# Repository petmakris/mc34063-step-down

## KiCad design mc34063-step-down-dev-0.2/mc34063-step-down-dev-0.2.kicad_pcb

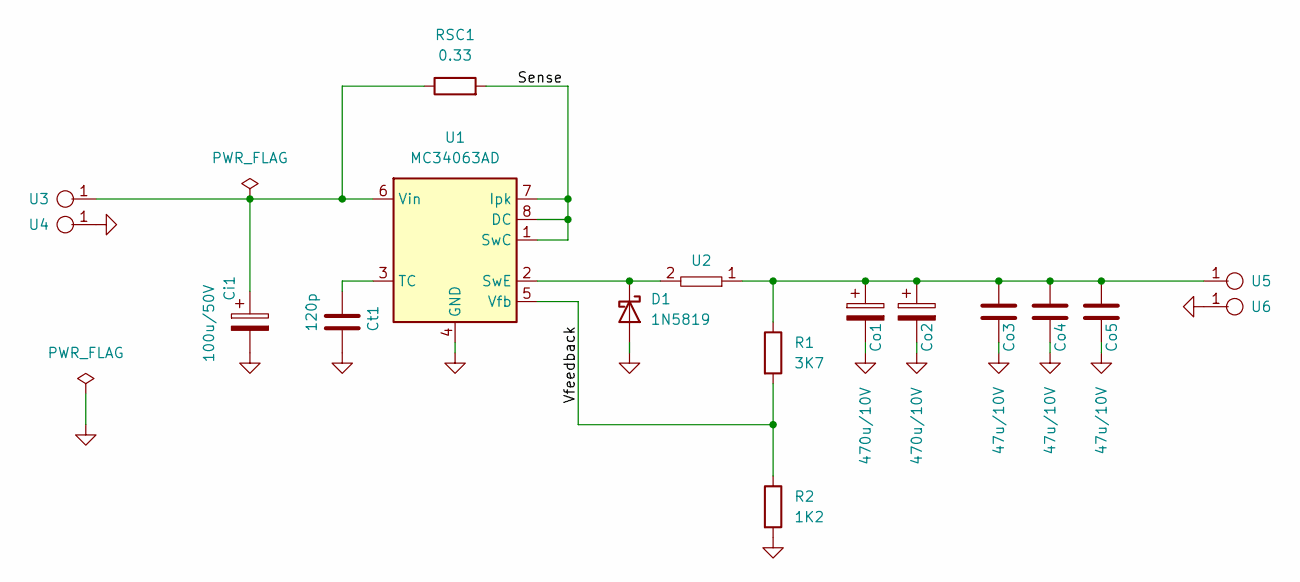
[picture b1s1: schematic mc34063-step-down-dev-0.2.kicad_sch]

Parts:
Ci1: 100u/50V; CP_Elec_6.3x7.7
Co1, Co2: 470u/10V; CP_Elec_6.3x7.7
Co3, Co4, Co5: 47u/10V; C_1206_3216Metric_Pad1.33x1.80mm_HandSolder
Ct1: 120p; C_0805_2012Metric_Pad1.18x1.45mm_HandSolder
D1: 1N5819; D_SOD-123
R1: 3K7; R_0805_2012Metric_Pad1.20x1.40mm_HandSolder
R2: 1K2; R_0805_2012Metric_Pad1.20x1.40mm_HandSolder
RSC1: 0.33; R_0805_2012Metric_Pad1.20x1.40mm_HandSolder
U1: MC34063AD; SOIC-8_3.9x4.9mm_P1.27mm
U2: mc34063-power-inductor-leaded
U3, U4, U5, U6: 1pin

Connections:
/Sense: RSC1.2, U1.1 (SwC), U1.7 (Ipk), U1.8 (DC)
/Vfeedback: R1.2, R2.1, U1.5 (Vfb)
GND: Ci1.2, Co1.2, Co2.2, Co3.2, Co4.2, Co5.2, Ct1.2, D1.2 (A), R2.2, U1.4 (GND), U4.1, U6.1
unnamed: Ci1.1, RSC1.1, U1.6 (Vin), U3.1
unnamed: Co1.1, Co2.1, Co3.1, Co4.1, Co5.1, R1.1, U2.1, U5.1
unnamed: Ct1.1, U1.3 (TC)
unnamed: D1.1 (K), U1.2 (SwE), U2.2

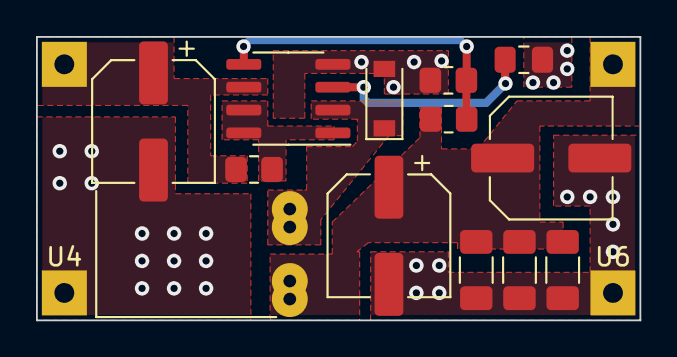
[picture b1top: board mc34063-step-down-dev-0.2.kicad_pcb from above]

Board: 2 copper layers, 33.5 x 15.7 mm, 17 parts (0 on the bottom side), 7 nets.

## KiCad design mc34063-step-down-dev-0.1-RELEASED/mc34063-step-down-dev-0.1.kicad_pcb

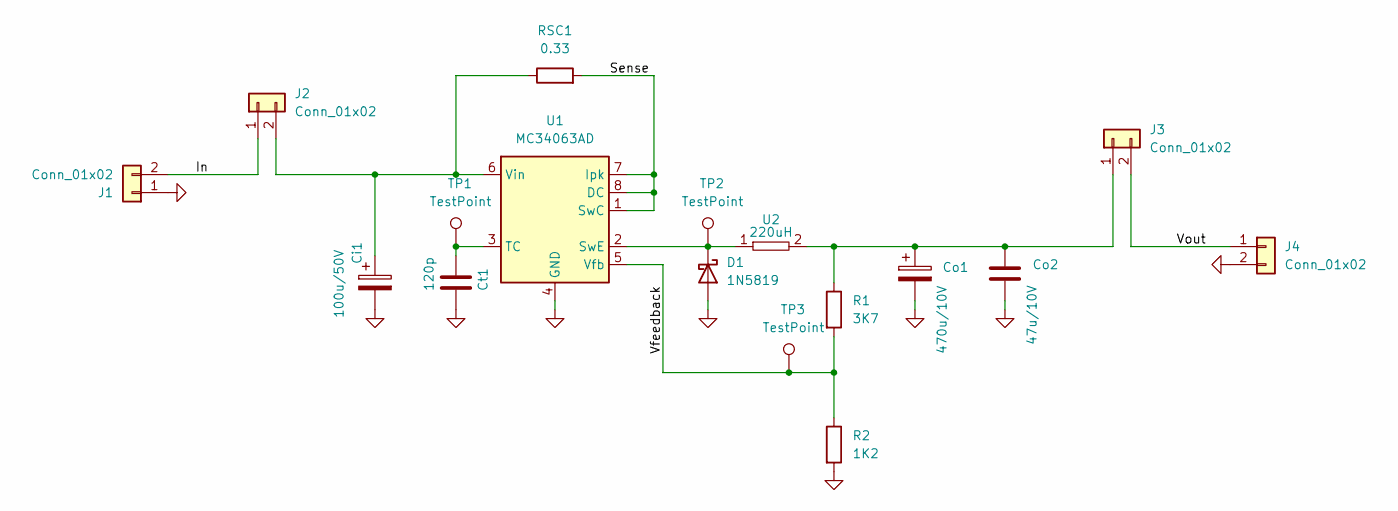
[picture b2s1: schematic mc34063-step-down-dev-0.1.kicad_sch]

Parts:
Ci1: 100u/50V; CP_Elec_6.3x7.7
Co1: 470u/10V; CP_Elec_6.3x7.7
Co2: 47u/10V; C_1206_3216Metric_Pad1.33x1.80mm_HandSolder
Ct1: 120p; C_0805_2012Metric_Pad1.18x1.45mm_HandSolder
D1: 1N5819; D_SOD-123
J1, J2, J3, J4: Conn_01x02; TerminalBlock_bornier-2_P5.08mm
R1: 3K7; R_0805_2012Metric_Pad1.20x1.40mm_HandSolder
R2: 1K2; R_0805_2012Metric_Pad1.20x1.40mm_HandSolder
RSC1: 0.33; R_0805_2012Metric_Pad1.20x1.40mm_HandSolder
TP1, TP2, TP3: TestPoint
U1: MC34063AD; SOIC-8_3.9x4.9mm_P1.27mm
U2: 220uH; mc34063-power-inductor

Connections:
/In: J1.2, J2.1
/Sense: RSC1.2, U1.1 (SwC), U1.7 (Ipk), U1.8 (DC)
/Vfeedback: R1.2, R2.1, TP3.1, U1.5 (Vfb)
/Vout: J3.2, J4.1
GND: Ci1.2, Co1.2, Co2.2, Ct1.2, D1.2 (A), J1.1, J4.2, R2.2, U1.4 (GND)
unnamed: Ci1.1, J2.2, RSC1.1, U1.6 (Vin)
unnamed: Co1.1, Co2.1, J3.1, R1.1, U2.2
unnamed: Ct1.1, TP1.1, U1.3 (TC)
unnamed: D1.1 (K), TP2.1, U1.2 (SwE), U2.1

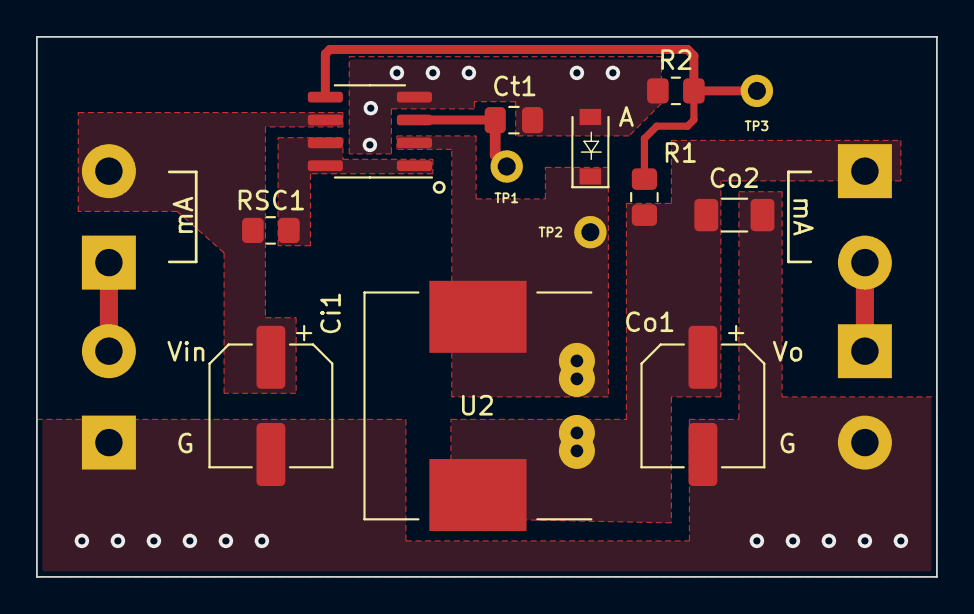
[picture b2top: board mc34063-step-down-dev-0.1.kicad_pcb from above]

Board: 2 copper layers, 50.0 x 30.0 mm, 17 parts (0 on the bottom side), 9 nets.

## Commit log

2022-10-09 released dev board
